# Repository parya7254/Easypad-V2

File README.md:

# Easypad-V2
A compact macropad featuring RGB lighting with SK6812 MINI-E Neopixel LEDs, a rotary encoder, a SSD1306 OLED Display and 15 (low-profile) choc mechanical switches! Powered by KMK firmware!

# Features:
Per-key RGB lighting via SK6812 MINI-E RGB LEDs, page scrolling via the onboard EC11 rotary encoder, a 0.91" 128x32 SSD1306 OLED display to display current mode, and 15 tactile low profile Kalih Choc V1 switches for compactability.

# Why?
I wanted to experiment with compact designs and Choc switches. I built this to help get the grasp of making keyboards/macropads with Kalih Choc switches since they have a different pin layout and are way more compact. I also wanted to make this because I really love designing hardware projects and PCBs in general every chance I get time.

# Flashing Firmware:
To flash the firmware to the macropad, first you will need to install CircuitPython onto the RPi Pico by first downloading the .uf2 file from the CircuitPython website and then dragging and dropping it to the USB Drive the Pico shows up as. Then, install KMK on it and then upload the code.py to the board. Instructions for installing KMK is on the KMK GitHub repo.

# Schematic:

# PCB:

# Previous PCB Revisions:

|  |  |  |
|-|-|-|

# CAD Link:
The assembled version is in Assembly 1!
https://cad.onshape.com/documents/4159a499467d346143555145/w/def90a5bdc25ba8320f86079/e/58cc027c9599ddc6d01a6483

# BOM:
| Part | Source | Quantity | Cost | Link |
|---|---|---|---|---|
| PCB | JLCPCB | 5 (MOQ) | $5.30 (with Shipping) | https://jlcpcb.com/ |
| Header Pins | AliExpress | 1 (comes with 5 male-female sets) | $1.79 | [Link](https://www.aliexpress.us/item/3256807049277042.html?spm=a2g0o.cart.0.0.79b838daFbyhMJ&mp=1&sourceType=570&pdp_npi=6%40dis%21USD%21USD+6.03%21USD+1.79%21%21USD+1.79%21%21%21%40210311c217847467351336984e0d3d%2112000039908542823%21ct%21US%21861143113%21%211%210%21&pdp_ext_f=%7B%22cart2PdpParams%22%3A%7B%22sourceType%22%3A%22570%22%2C%22cartSource%22%3A%22main%22%7D%7D&gatewayAdapt=glo2usa) |
| RPi Pico (clone) | AliExpress | 1 | $2.79 | [Link](https://www.aliexpress.us/item/3256807207612469.html?spm=a2g0o.cart.0.0.79b838daFbyhMJ&mp=1&sourceType=570&pdp_npi=6%40dis%21USD%21USD+8.63%21USD+2.59%21%21USD+2.59%21%21%21%40210311c217847467351336984e0d3d%2112000040565295947%21ct%21US%21861143113%21%211%210%21&pdp_ext_f=%7B%22cart2PdpParams%22%3A%7B%22sourceType%22%3A%22570%22%2C%22cartSource%22%3A%22main%22%7D%7D&gatewayAdapt=glo2usa) |
| 128x32 OLED | AliExpress | 1 | $1.99 | [Link](https://www.aliexpress.us/item/3256807613276538.html?spm=a2g0o.cart.0.0.79b838daFbyhMJ&mp=1&sourceType=570&pdp_npi=6%40dis%21USD%21USD+3.38%21USD+1.99%21%21USD+1.99%21%21%21%40210311c217847467351336984e0d3d%2112000042242093250%21ct%21US%21861143113%21%211%210%21&pdp_ext_f=%7B%22cart2PdpParams%22%3A%7B%22sourceType%22%3A%22570%22%2C%22cartSource%22%3A%22main%22%7D%7D&gatewayAdapt=glo2usa) |
| Switches | AliExpress | 2 sets of 10pcs | $5.79 | [Link](https://www.aliexpress.us/item/3256811626047380.html?spm=a2g0o.cart.0.0.79b838daFbyhMJ&mp=1&pdp_npi=6%40dis%21USD%21USD+6.11%21USD+5.79%21%21USD+5.79%21%21%21%40210311c217847467351336984e0d3d%2112000056648742495%21ct%21US%21861143113%21%212%210%21&gatewayAdapt=glo2usa) |
| 1N4148W Diodes | AliExpress | 100 | $1.48 | [Link](https://www.aliexpress.us/item/3256804920500448.html?spm=a2g0o.cart.0.0.79b838daFbyhMJ&mp=1&pdp_npi=6%40dis%21USD%21USD+1.48%21USD+1.48%21%21USD+1.48%21%21%21%40210311c217847467351336984e0d3d%2112000031683474020%21ct%21US%21861143113%21%211%210%21&gatewayAdapt=glo2usa) |
| SK6812 Mini E LEDs | AliExpress | 100pcs | $7.33 | [Link](https://www.aliexpress.us/item/3256810305129996.html?spm=a2g0o.cart.0.0.79b838daFbyhMJ&mp=1&pdp_npi=6%40dis%21USD%21USD+7.33%21USD+7.33%21%21USD+7.33%21%21%21%40210311c217847467351336984e0d3d%2112000052582134405%21ct%21US%21861143113%21%211%210%21&gatewayAdapt=glo2usa) |
| Rotary Encoder | AliExpress | 5 | $3.58 | [Link](https://www.aliexpress.us/item/2255799842376254.html?spm=a2g0o.cart.0.0.79b838daFbyhMJ&mp=1&pdp_npi=6%40dis%21USD%21USD+3.58%21USD+2.58%21%21USD+2.58%21%21%21%40210311c217847467351336984e0d3d%2110000000064746984%21ct%21US%21861143113%21%211%210%21&gatewayAdapt=glo2usa) |
| Black Keycaps | AliExpress | 20 | $5.61 | [Link](https://www.aliexpress.us/item/3256810543438304.html?spm=a2g0o.cart.0.0.79b838daFbyhMJ&mp=1&pdp_npi=6%40dis%21USD%21USD+5.59%21USD+5.59%21%21USD+5.59%21%21%21%40210311c217847467351336984e0d3d%2112000053333576164%21ct%21US%21861143113%21%211%210%21&gatewayAdapt=glo2usa) |
| Screws | AliExpress | 1 Kit with Different Sizes | $2.05 | [Link](https://www.aliexpress.us/item/2255799870438450.html?spm=a2g0o.productlist.main.1.6b875acd6flyr6&algo_pvid=6b10e474-3676-4871-92a7-8eb7f06ff66c&algo_exp_id=6b10e474-3676-4871-92a7-8eb7f06ff66c-0&pdp_ext_f=%7B%22order%22%3A%226671%22%2C%22eval%22%3A%221%22%2C%22fromPage%22%3A%22search%22%7D&pdp_npi=6%40dis%21USD%213.26%212.78%21%21%213.26%212.78%21%40210311c217941784485231567e103b%2110000000227171460%21sea%21US%21861143113%21X%211%210%21n_tag%3A-29919%3Bd%3Acd0c5907%3Bm03_new_user%3A-29895%3BpisId%3A5000000220844609&curPageLogUid=CKpxbTIenidI&utparam-url=scene%3Asearch%7Cquery_from%3A%7Cx_object_id%3A4000056753202%7C_p_origin_prod%3A)
| Total Cost: | - | - | $37.71 | - |

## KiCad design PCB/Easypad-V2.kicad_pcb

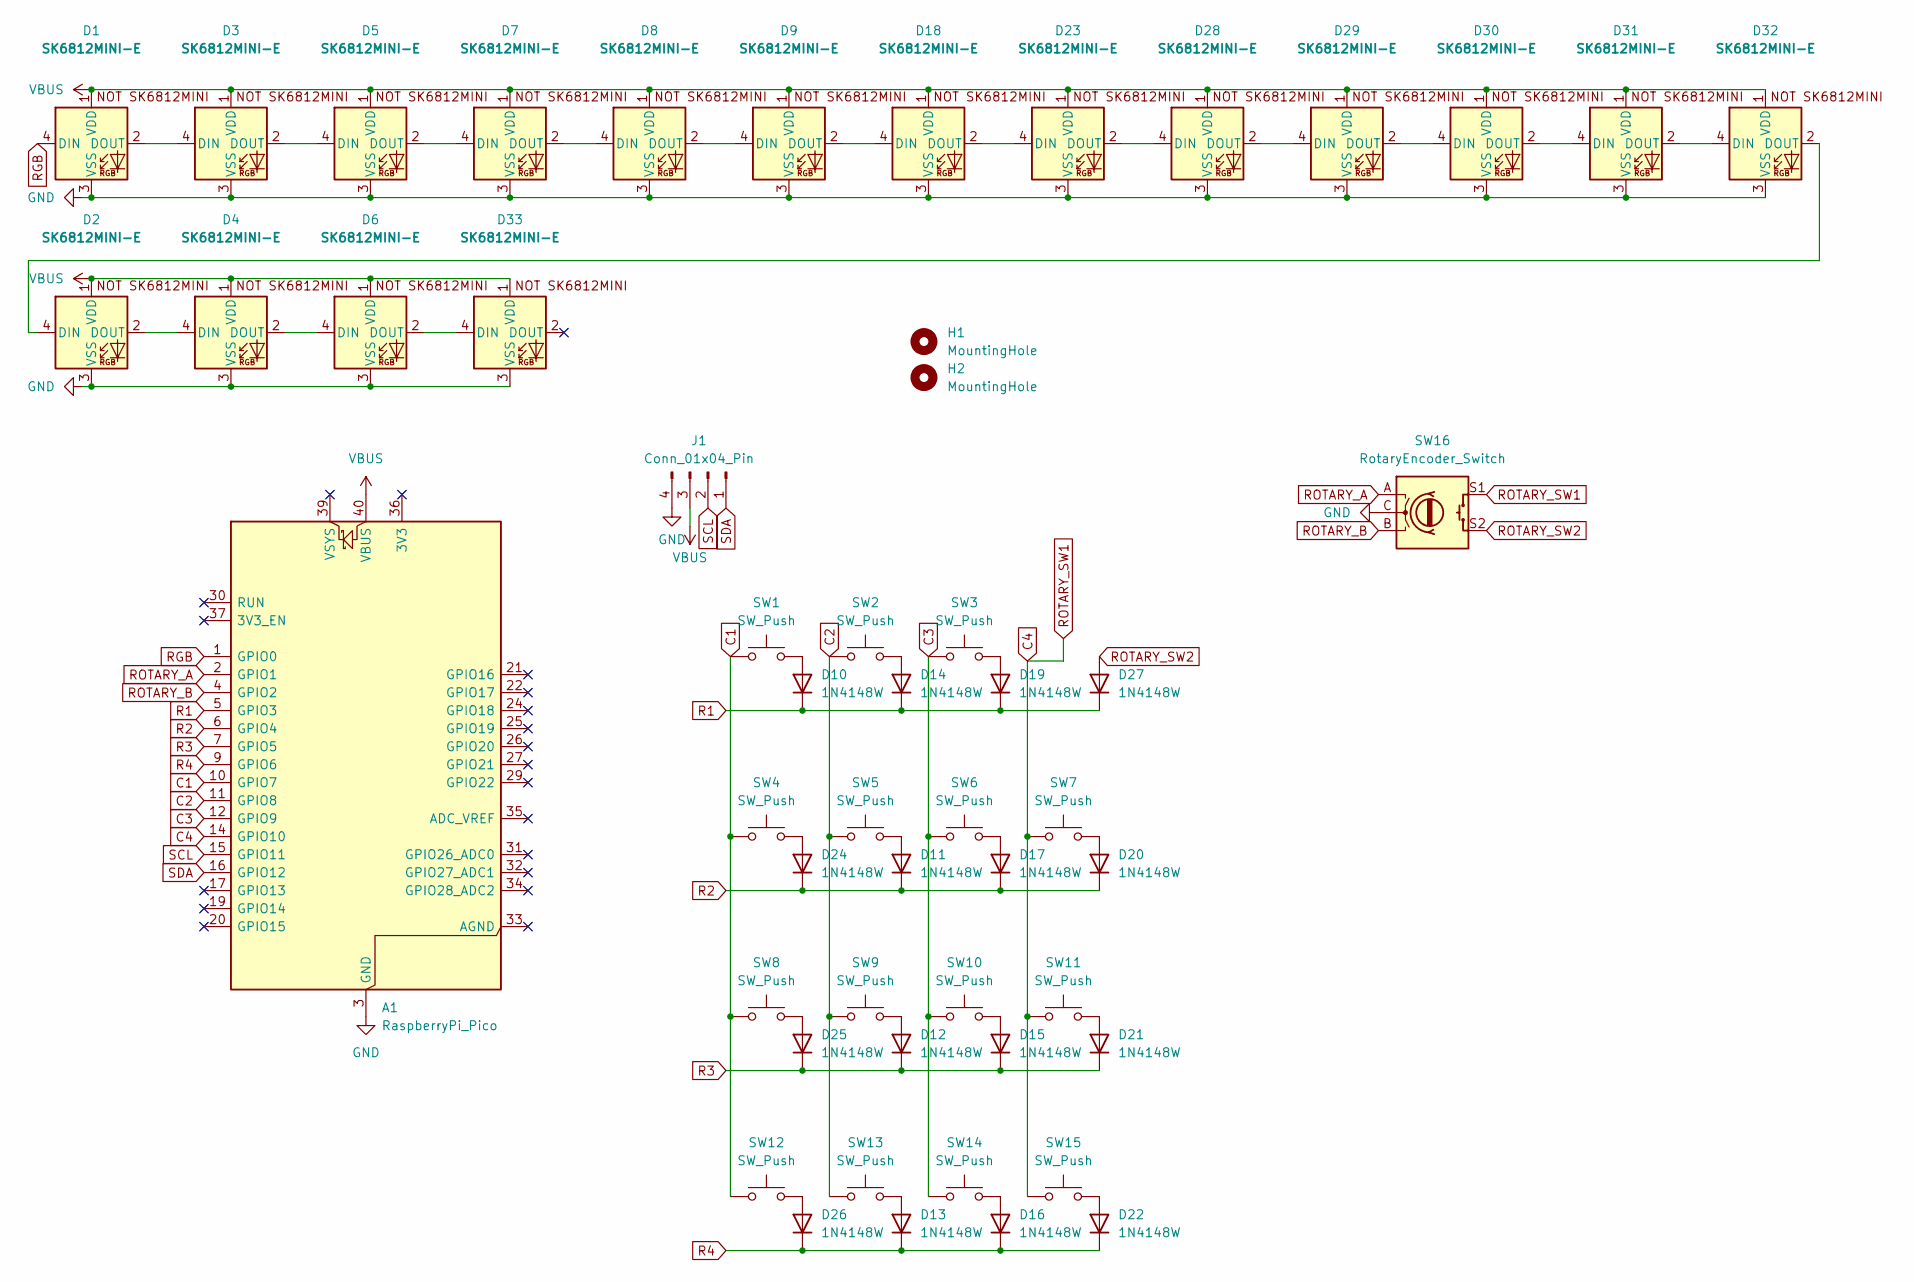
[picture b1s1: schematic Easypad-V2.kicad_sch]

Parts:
A1: RaspberryPi_Pico; RaspberryPi_Pico_Common_Unspecified
D1, D2, D3, D4, D5, D6, D7, D8, D9, D18, D23, D28, D29, D30, D31, D32, D33: SK6812MINI-E; MX_SK6812MINI-E_REV
D10, D11, D12, D13, D14, D15, D16, D17, D19, D20, D21, D22, D24, D25, D26, D27: 1N4148W; D_SOD-123
H1, H2: MountingHole; MountingHole_2.2mm_M2
J1: Conn_01x04_Pin; PinHeader_1x04_P2.54mm_Vertical
SW1, SW2, SW3, SW4, SW5, SW6, SW7, SW8, SW9, SW10, SW11, SW12, SW13, SW14, SW15: SW_Push; Choc_V1_1.00u
SW16: RotaryEncoder_Switch; RotaryEncoder_Alps_EC11E-Switch_Vertical_H20mm

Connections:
C1: A1.10 (GPIO7), SW1.1, SW4.1, SW8.1, SW12.1
C2: A1.11 (GPIO8), SW2.1, SW5.1, SW9.1, SW13.1
C3: A1.12 (GPIO9), SW3.1, SW6.1, SW10.1, SW14.1
C4: A1.14 (GPIO10), SW7.1, SW11.1, SW15.1, SW16.S1
GND: A1.3 (GND), A1.8 (GND), A1.13 (GND), A1.18 (GND), A1.23 (GND), A1.28 (GND), A1.38 (GND), D1.3 (VSS), D2.3 (VSS), D3.3 (VSS), D4.3 (VSS), D5.3 (VSS), D6.3 (VSS), D7.3 (VSS), D8.3 (VSS), D9.3 (VSS), D18.3 (VSS), D23.3 (VSS), D28.3 (VSS), D29.3 (VSS), D30.3 (VSS), D31.3 (VSS), D32.3 (VSS), D33.3 (VSS), J1.4, SW16.C
unnamed: D1.2 (DOUT), D3.4 (DIN)
unnamed: D2.4 (DIN), D32.2 (DOUT)
unnamed: D2.2 (DOUT), D4.4 (DIN)
unnamed: D3.2 (DOUT), D5.4 (DIN)
unnamed: D4.2 (DOUT), D6.4 (DIN)
unnamed: D5.2 (DOUT), D7.4 (DIN)
unnamed: D7.2 (DOUT), D8.4 (DIN)
unnamed: D8.2 (DOUT), D9.4 (DIN)
unnamed: D10.2 (A), SW1.2
unnamed: D11.2 (A), SW5.2
unnamed: D12.2 (A), SW9.2
unnamed: D13.2 (A), SW13.2
unnamed: D14.2 (A), SW2.2
unnamed: D15.2 (A), SW10.2
unnamed: D16.2 (A), SW14.2
unnamed: D17.2 (A), SW6.2
unnamed: D9.2 (DOUT), D18.4 (DIN)
unnamed: D18.2 (DOUT), D23.4 (DIN)
unnamed: D19.2 (A), SW3.2
unnamed: D20.2 (A), SW7.2
unnamed: D21.2 (A), SW11.2
unnamed: D22.2 (A), SW15.2
unnamed: D23.2 (DOUT), D28.4 (DIN)
unnamed: D24.2 (A), SW4.2
unnamed: D25.2 (A), SW8.2
unnamed: D26.2 (A), SW12.2
unnamed: D28.2 (DOUT), D29.4 (DIN)
unnamed: D29.2 (DOUT), D30.4 (DIN)
unnamed: D30.2 (DOUT), D31.4 (DIN)
unnamed: D31.2 (DOUT), D32.4 (DIN)
unnamed: D6.2 (DOUT), D33.4 (DIN)
R1: A1.5 (GPIO3), D10.1 (K), D14.1 (K), D19.1 (K), D27.1 (K)
R2: A1.6 (GPIO4), D11.1 (K), D17.1 (K), D20.1 (K), D24.1 (K)
R3: A1.7 (GPIO5), D12.1 (K), D15.1 (K), D21.1 (K), D25.1 (K)
R4: A1.9 (GPIO6), D13.1 (K), D16.1 (K), D22.1 (K), D26.1 (K)
RGB: A1.1 (GPIO0), D1.4 (DIN)
ROTARY_A: A1.2 (GPIO1), SW16.A
ROTARY_B: A1.4 (GPIO2), SW16.B
ROTARY_SW2: D27.2 (A), SW16.S2
SCL: A1.15 (GPIO11), J1.2
SDA: A1.16 (GPIO12), J1.1
VBUS: A1.40 (VBUS), D1.1 (VDD), D2.1 (VDD), D3.1 (VDD), D4.1 (VDD), D5.1 (VDD), D6.1 (VDD), D7.1 (VDD), D8.1 (VDD), D9.1 (VDD), D18.1 (VDD), D23.1 (VDD), D28.1 (VDD), D29.1 (VDD), D30.1 (VDD), D31.1 (VDD), D32.1 (VDD), D33.1 (VDD), J1.3

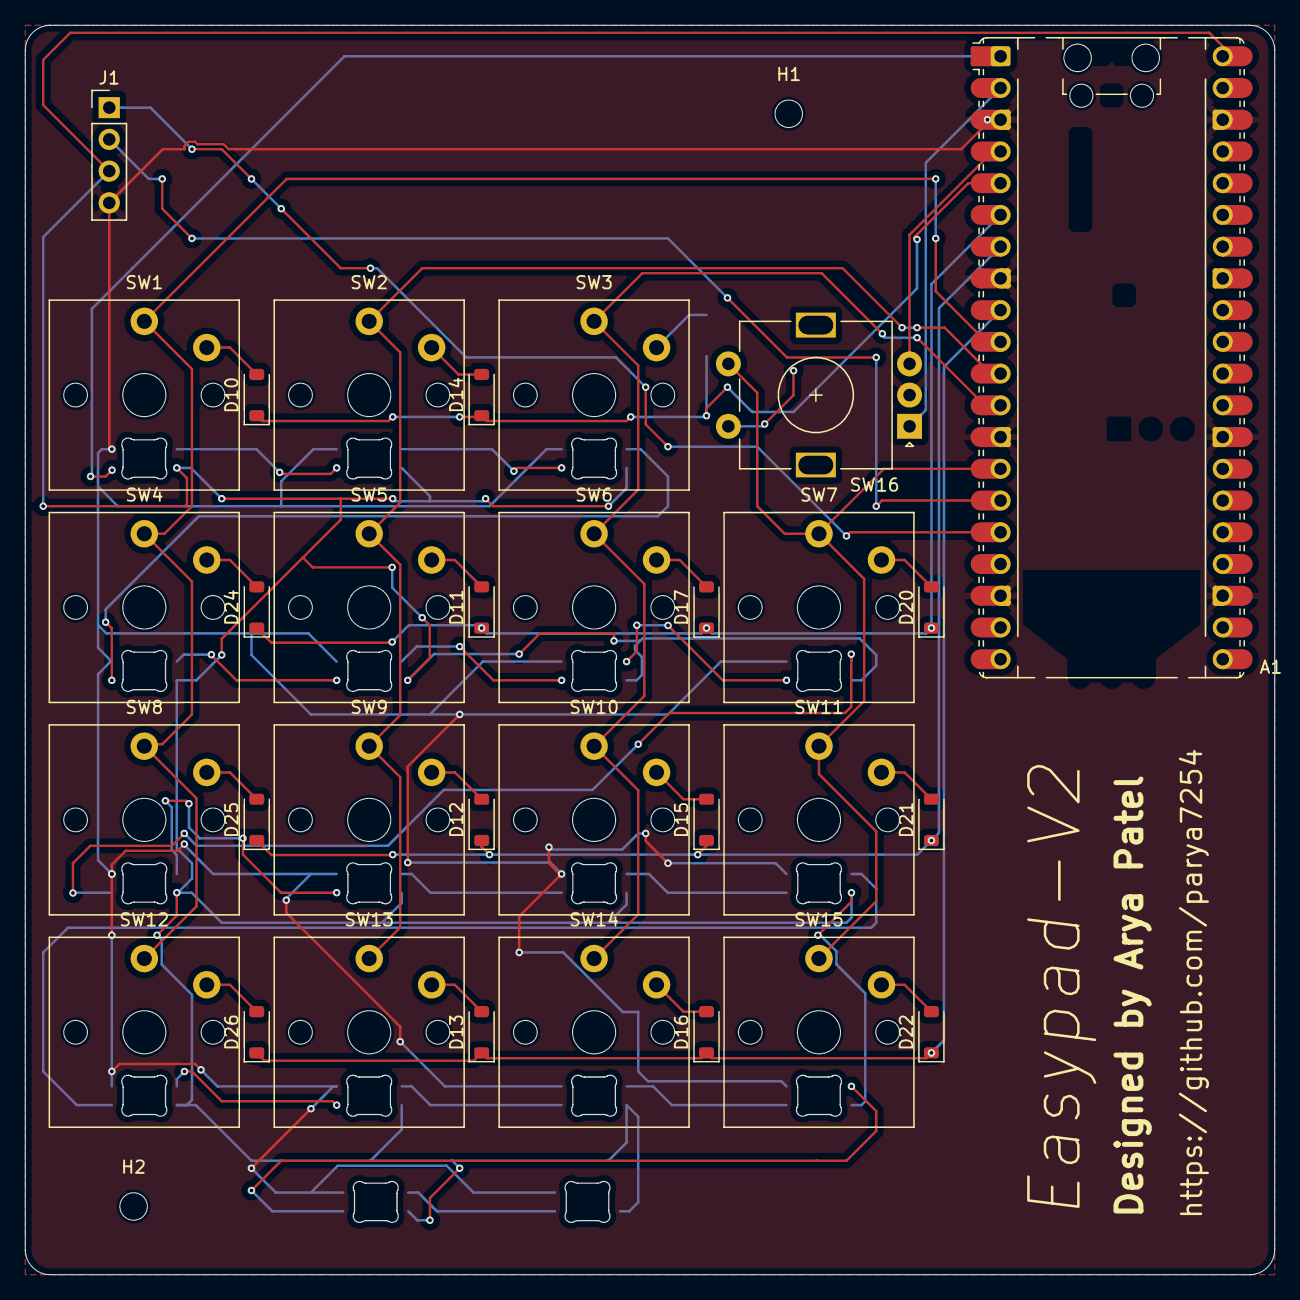
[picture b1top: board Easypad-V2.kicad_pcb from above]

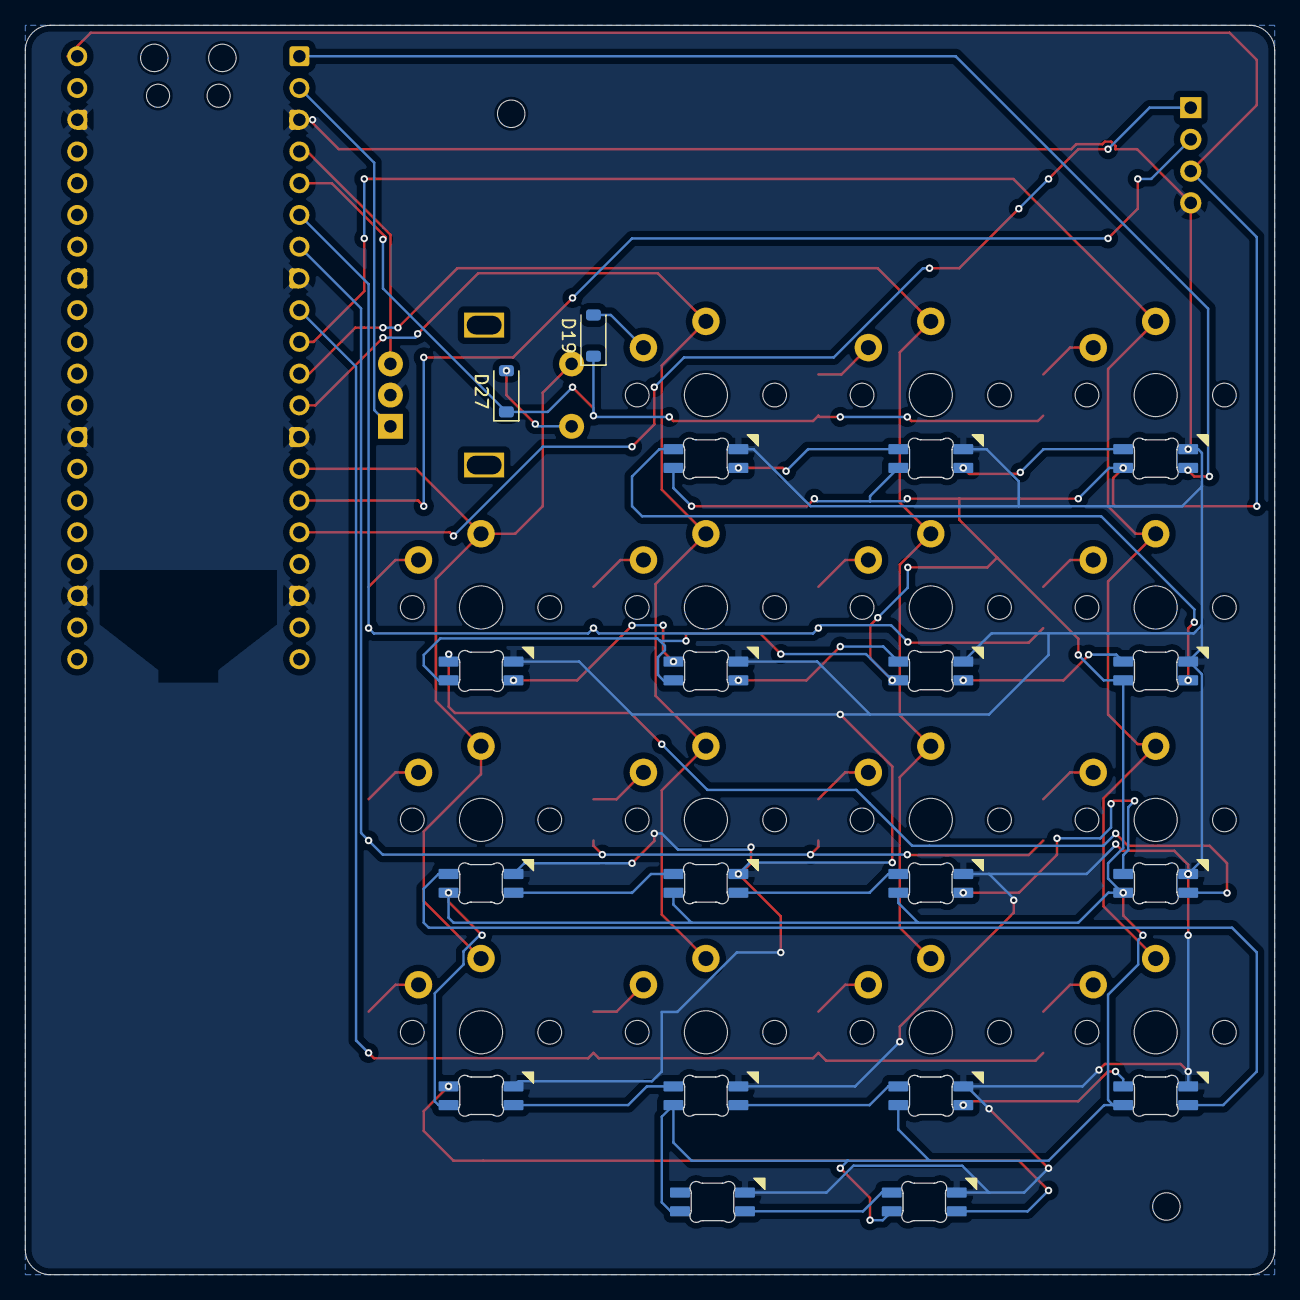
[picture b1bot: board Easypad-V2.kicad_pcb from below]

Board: 2 copper layers, 100.0 x 100.0 mm, 53 parts (2 on the bottom side), 47 nets.
